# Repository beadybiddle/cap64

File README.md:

# cap64
Capacitive touch slider daughterboard for use in the bd64 keyboard.

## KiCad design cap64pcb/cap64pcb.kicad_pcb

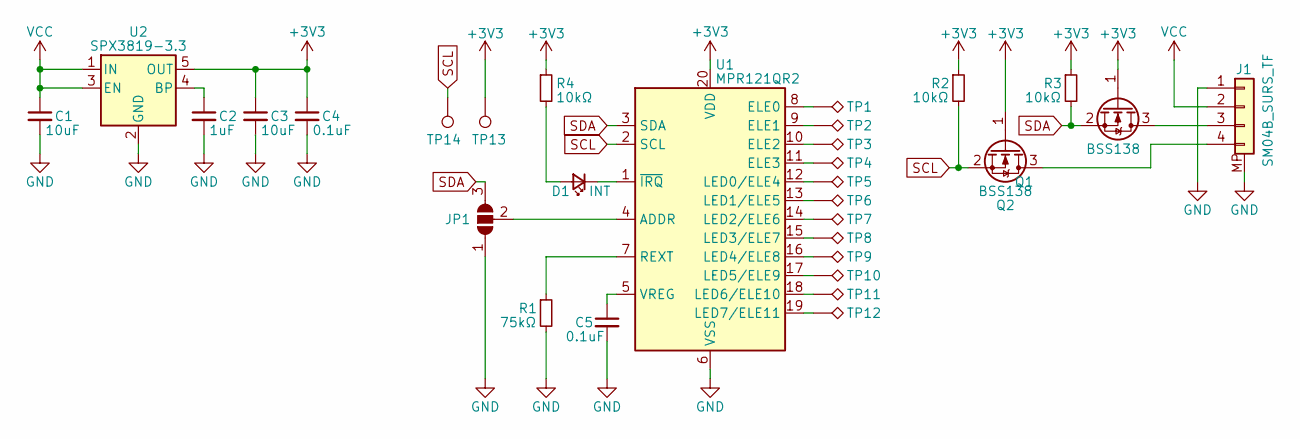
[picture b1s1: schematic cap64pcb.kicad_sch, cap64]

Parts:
C1, C3: 10uF; C_0805_2012Metric
C2: 1uF; C_0805_2012Metric
C4, C5: 0.1uF; C_0805_2012Metric
D1: INT; LED_0805_2012Metric
J1: SM04B_SURS_TF; JST_SUR_SM04B-SURS-TF_1x04-1MP_P0.80mm_Horizontal
JP1: SolderJumper_3_Open; SolderJumper-3_P1.3mm_Open_RoundedPad1.0x1.5mm_NumberLabels
Q1, Q2: BSS138; SOT-23
R1: 75kΩ; R_0805_2012Metric
R2, R3, R4: 10kΩ; R_0805_2012Metric
TP1: TestPoint_Alt; CAPPADS_7.6x11.6_Chevron_1
TP2, TP3, TP4, TP5, TP6, TP7, TP8, TP9, TP10, TP11: TestPoint_Alt; CAPPADS_7.6x11.6_Chevron_2
TP12: TestPoint_Alt; CAPPADS_7.6x11.6_Chevron_3
TP13: b; TestPoint_Pad_2.0x2.0mm
TP14: d; TestPoint_Pad_2.0x2.0mm
U1: MPR121QR2; UQFN-20_3x3mm_P0.4mm
U2: SPX3819-3.3; SOT-23-5

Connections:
+3V3: C3.1, C4.1, Q1.1 (G), Q2.1 (G), R2.1, R3.1, R4.1, TP13.1, U1.20 (VDD), U2.5 (OUT)
GND: C1.2, C2.2, C3.2, C4.2, C5.2, J1.1, J1.MP, JP1.1 (A), R1.2, U1.6 (VSS), U2.2 (GND)
unnamed: C2.1, U2.4 (BP)
unnamed: C5.1, U1.5 (VREG)
unnamed: D1.2 (A), R4.2
unnamed: J1.3, Q1.3 (D)
unnamed: J1.4, Q2.3 (D)
unnamed: R1.1, U1.7 (REXT)
unnamed: TP1.1, U1.8 (ELE0)
unnamed: TP2.1, U1.9 (ELE1)
unnamed: TP3.1, U1.10 (ELE2)
unnamed: TP4.1, U1.11 (ELE3)
unnamed: TP5.1, U1.12 (LED0/ELE4)
unnamed: TP6.1, U1.13 (LED1/ELE5)
unnamed: TP7.1, U1.14 (LED2/ELE6)
unnamed: TP8.1, U1.15 (LED3/ELE7)
unnamed: TP9.1, U1.16 (LED4/ELE8)
unnamed: TP10.1, U1.17 (LED5/ELE9)
unnamed: TP11.1, U1.18 (LED6/ELE10)
unnamed: TP12.1, U1.19 (LED7/ELE11)
unnamed: D1.1 (K), U1.1 (~IRQ)
unnamed: JP1.2 (C), U1.4 (ADDR)
SCL: Q2.2 (S), R2.2, TP14.1, U1.2 (SCL)
SDA: JP1.3 (B), Q1.2 (S), R3.2, U1.3 (SDA)
VCC: C1.1, J1.2, U2.1 (IN), U2.3 (EN)

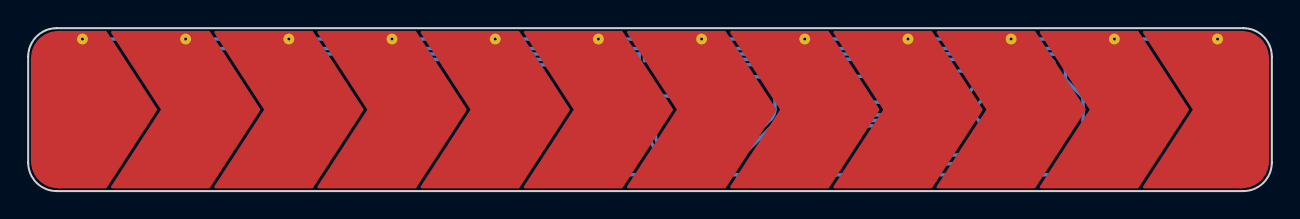
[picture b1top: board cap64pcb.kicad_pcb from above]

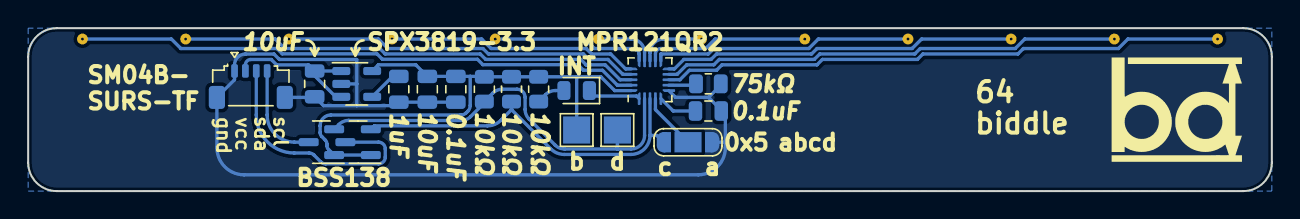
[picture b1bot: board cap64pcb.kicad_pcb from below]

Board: 2 copper layers, 91.6 x 12.0 mm, 30 parts (18 on the bottom side), 25 nets.

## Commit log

2022-06-15 sch init
2022-06-22 first draft sch
2022-06-22 pullup i2c 3v3 side lines
2022-06-22 cap pads
2022-06-22 rounded chevron pad corners
2022-06-22 reworked chevrons (merged pads, shrunk to 7.6)
2022-06-22 fixed miniscule spacing error
2022-06-22 shifted 'via' for center pads
2022-06-22 routed pads 7-12
2022-06-22 rough 1-6 routing
2022-06-22 pinout no longer all 1s
2022-06-22 shifted PTH up on touch pads
2022-06-22 rerouted pads
2022-06-22 cleaning silks
2022-06-22 prep for embiggening
2022-06-22 taller touchpad footprints
2022-06-22 updated sch and pcb with taller pads
2022-06-22 shrunk pad radii by 0.01mm
2022-06-22 prepping silks
2022-06-22 arranging components
2022-06-22 test traces
2022-06-22 remove test traces
2022-06-22 4pin, IRQ LED
2022-06-22 update pcb
2022-06-22 reorder conn pinout
2022-06-22 tie MP to GND
2022-06-22 better routing
2022-06-22 unroutable.?
2022-06-22 logo and up to ADDR jumpers
2022-06-22 pretty!
2022-06-22 shift up addr silk
2022-06-22 remove shunt lib
2022-06-22 half filleted
2022-06-22 shifted caps/resistors up a smidge
2022-06-22 reconnect cap gnd pins
2022-06-23 power outage oopsie
2022-06-23 mpr121 3d model
2022-06-23 connector 3d model
2022-06-23 step export
